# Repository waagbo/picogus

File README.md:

# PicoGUS THT

PicoGUS is a Raspberry Pi Pico based ISA sound card for DOS and Win9x retro computers.
It is a highly versatile clone card that provides near perfect emulation of the Gravis Ultrasound, Sound Blaster-series, AdLib, Tandy 3-voice and CMS/Game Blaster.

Additional features like CD-ROM (Panasonic MKE), MPU-401 and USB game controllers build further on the cards versatility and the wavetable header will further extend the capacity with a card like [X2GS from Serdaco](https://serdashop.com/products/x2gs-te) to get the original Roland magic or even a [WavetablePi](https://github.com/scrapcomputing/WavetablePiHoriz) for the ultimate all-in-one experience for MS-DOS games. 

**PicoGUS THT is a through-hole conversion of the [PicoGUS project](https://github.com/polpo/picogus).**<br />
The conversion introduces through-hole components where possible in addition to embedding new features and ideas while still keeping the card compatible with the upstream project. The design goal is to make the project be easier to solder by hand as well as giving it a higher level of retro asthetics.

PicoGUS THT exists in multiple variants based on different PicoGUS revisions. Each variant is found in their separate folder (or branch if still experimental). The different *hw* designs feature additional documentation including ready to order BOM CSVs in their respective *docs* folders.

The designs still have some TSSOP SMD chips as they do not have THT equivalents, namely the two *SN74CB3T3257PWR* level shifters (U3/U4) as well as the PCM510xA DAC. PicoGUS THT features a redesigned footprint to ease debugging in case something goes wrong.

**Note!** The hardware revisions are intentionally kept aligned with the *major* revision as the original PicoGUS boards. This is done to indicate hardware feature compatibility and to prevent confusion in case of any future major revisions of the original PicoGUS design.

### Version 1.3
This version is an extension of the PicoGUS 1.2 design while implementing the *wavetable header* with manual volume control from the *hw-hand386* branch. Together with the addition of a full size USB-A connector accessible from the computers backside this card is now a real competitor to the v2.0 SMD design.

In addition, the THT boards have also been slightly resized to optimize for component placement and JCLPCB-pricing. Progress wise, the initial design idea has been built and tested. The release version v1.3.2 is still pending build/test.

Assembly should be *EASY to MEDIUM* with the appropriate quality tools and consumables and a good project for beginners that want a little more challenge. Here is a list of recommended supplies with some personal recommendations:
* [Low Temperature Solder Paste](https://www.digikey.com/en/products/detail/chip-quik-inc/NC191LTA10/13531404) for easy soldering of SMD components.
* [Flux](https://www.digikey.com/en/products/detail/chip-quik-inc/NC191-2CC6/11480375) as it makes solder behave like magic when you need it the most.
* [Solder Wick](https://www.digikey.com/en/products/detail/chemtronics/SW14035/5177685) as it will help you when flux can't. Remember to **NEVER** pull a stuck wick.
* [Soldering Iron with J-Tip (Alientek T90B)](https://www.aliexpress.com/item/1005010015046346.html) will make the SMD components a breeze to solder. 
* [Tweezers](https://www.aliexpress.com/item/1005007298021096.html) for handling the SMD components.
* Digital Microscope of decent quality from AliExpress is very useful for visual inspection of SMD chips.
* Multimeter with good continuity tester.

### Version 2.1
This is an experimental extension of the PicoGUS 2.0 SMD design, made possible using a Waveshare Core2350B board to free enough I/O ports for the 2.0 feature set. This is still in the design phase.
<br/>

### Experimental Software Features
We have added experimental features that adds upon community ideas on top of the original software. The features are submitted as Pull Requests to the original PicoGUS repository as well but there is no guarantee that they will ever be included in the official software releases:
* DFS drive support inspired by PicoMEM so the USB drive can be accessed from MS-DOS.

<br/>

**A big thank you to [Ian Scott (polpo)](https://github.com/polpo/) for the PicoGUS design and his contributions to the retro community.**<br/>**May his work set an example for future open-source hardware projects.**

--<br/>
Vidar Waagbø, Retro City AS

## PicoGUS

The original PicoGUS project is found at [polpo/pigocus](https://github.com/polpo/picogus) or www.picogus.com.<br/>
Here are the original README.md to give some more information about the great features of the PicoGUS:

ISA sound card and CD-ROM drive emulation on the Raspberry Pi Pico's RP2040 microcontroller. PicoGUS can emulate:

* [Gravis Ultrasound (GUS)](https://en.wikipedia.org/wiki/Gravis_Ultrasound) - the primary focus of PicoGUS, hence the name
* [Sound Blaster 16](https://en.wikipedia.org/wiki/Sound_Blaster_16) (OPL3) / [Sound Blaster Pro 2](https://en.wikipedia.org/wiki/Sound_Blaster#Sound_Blaster_Pro_2,_CT1600) (OPL3) / [AdLib](https://en.wikipedia.org/wiki/Ad_Lib,_Inc.) (OPL2)
* [MPU-401 (with intelligent mode)](https://en.wikipedia.org/wiki/MPU-401) - outputs MIDI data on 3.5mm MIDI TRS connector
* [Tandy 3-voice](http://www.vgmpf.com/Wiki/index.php?title=Tandy_3_Voice)
* [CMS/Game Blaster](http://nerdlypleasures.blogspot.com/2012/10/all-you-ever-wanted-to-know-about.html)
* [Game port joystick](https://en.wikipedia.org/wiki/Game_port)
* [Panasonic/MKE CD-ROM](https://en.wikipedia.org/wiki/Panasonic_CD_interface)

Current status: perpetual beta! See the [main wiki page](https://github.com/polpo/picogus/wiki) for current status and the [compatibility list](https://github.com/polpo/picogus/wiki/Compatibility-list) for support status of various DOS programs and other system compatibility notes. This project has a heavy demoscene focus due to the GUS's history so that's what I've concentrated on, but GUS support in games is very good to excellent.

Want to buy a PicoGUS? Fully assembled PicoGUS 2.0 sound cards are available from these sources, all of whom ship worldwide:

* [Joe's Computer Museum Shop](https://jcm-1.com/product/picogus-v2/) - in US 🇺🇸
* [Serdashop](https://www.serdashop.com/PicoGUS) - in EU 🇪🇺
* [Flamelily IT](https://shop.flamelily.co.uk/picogus) - in UK 🇬🇧

Want to make your own PicoGUS? See the [build guide](https://github.com/polpo/picogus/wiki/Building-your-PicoGUS). Note that the more DIY friendly v1.1.1 hardware has some documented issues with reset – a forthcoming v1.2 revision will fix these issues. **Important caveat**: due to the specs of the Pico, assumptions made by programs written to use the GUS, the imprecise nature of emulation, and the varying specs of retro DOS PC hardware, some things will likely never be perfect. **This is still a work in progress.**

Have a PicoGUS and want to use it? See the [configuring and using your PicoGUS guide](https://github.com/polpo/picogus/wiki/Configuring-and-using-your-PicoGUS).

Want to support PicoGUS? I have a limited number of machines to test PicoGUS in and donating either money or motherboards would be greatly appreciated and help increase the compatibility of PicoGUS.

You can donate via [PayPal](https://paypal.me/ianpolpo) or Ko-Fi: 

See/hear PicoGUS in action on YouTube:

Videos by others:

My videos:

## Open Source Credits

* [Raspberry Pi Pico C/C++ SDK](https://github.com/raspberrypi/pico-sdk)
* `pico_audio_i2s` from [pico-extras](https://github.com/raspberrypi/pico-extras)
* `stdio_async_uart` from [PicoCart64](https://github.com/kbeckmann/PicoCart64)
* `gus-x.cpp` adapted from [DOSBox-X](https://github.com/joncampbell123/dosbox-x)
* OPL/AdLib emulation from [rp2040-doom](https://github.com/kilograham/rp2040-doom) (based on [emu8950](https://github.com/digital-sound-antiques/emu8950))
* MPU-401 emulation adapted from [HardMPU](https://github.com/ab0tj/HardMPU) and [DOSBox-X](https://github.com/joncampbell123/dosbox-x)
* Tandy 3-voice emulation based on code contributed by [Aaron Giles](https://aarongiles.com/), adapted from [DREAMM](https://aarongiles.com/dreamm/) 
* CMS emulation based on code contributed by [Aaron Giles](https://aarongiles.com/), adapted from [DREAMM](https://aarongiles.com/dreamm/)
* USB support uses [TinyUSB](https://github.com/hathach/tinyusb) and [tusb_xinput](https://github.com/Ryzee119/tusb_xinput) with USB mass storage improvements by rppicomidi and wbcbz7.
* FAT drive support by [FatFS](https://elm-chan.org/fsw/ff/)

## License

The hardware portions of this repository (hw/ directory) are licensed under the CERN OHL version 2, permissive.

The software portions of this repository (sw/, pgusinit/ directories) as a collection are licensed under the GNU GPL version 2. Some files are individually dual-licensed under BSD or MIT licenses – see the license in the file headers for details.

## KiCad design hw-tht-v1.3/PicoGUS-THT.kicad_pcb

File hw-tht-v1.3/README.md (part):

# PicoGUS THT (through-hole) v1.3.2 – based on PicoGUS v1.2

Board revision **v1.3.2**: the v1.3.1 (rev B) THT board on a 102 mm outline, with
the fine-pitch chips soldered straight to the card and a test pad on every one of their pins.

* **U3/U4** (SN74CB3T3257, TSSOP-16) and **U9** (PCM5102A, TSSOP-20; the PCM5100A/5101A fit too) only exist as TSSOPs. They are soldered to
  the card on hand-solder footprints, and **every pin has its own 0.7 mm round test pad** in line with it, for a
  probe, a meter or a scope (see [U3/U4 and U9 with a test pad per pin](#u3u4-and-u9-with-a-test-pad-per-pin)).
  The TSSOP-to-DIP adapter boards of the earlier v1.3.2 layout are gone, and so are their sockets.
* **The GY-PCM5102 module option (J10) is gone.** The on-board DAC is always fitted.
* **New placement** of the DAC block, the mixer and the jacks (2026-10-31 / 2026-11-01): the DAC sits above U3/U4
  with its analog side facing east toward the output filter and the mixer above it, MIDI OUT at the top of the
  bracket end and LINE OUT below WT VOL (see [Placement](#placement)).
* **C36** (U9 charge-pump decoupling) is a through-hole 0.1 µF disc, and all eight DAC decoupling discs sit on the
  side of U9 where their pins are (see [DAC decoupling](#dac-decoupling)).
* **C8/C10** (U8 PSRAM decoupling) are the v1.3.1 through-hole discs, next to U8.
* **1.84 mm shorter**: 102.0 mm long over the outline (v1.3.1: 103.8 mm), trimmed at the bracket end. The bracket tab
  holes H1/H2 are 1.70 mm further from the bracket plate, so the card needs a bracket with longer tabs (see
  [Bracket](#bracket)).
* **No artwork on the back silkscreen**: the princess artwork is to be UV printed instead. The back texts stay.

The main board is through-hole apart from **U3, U4, U9** (TSSOP, 0.65 mm pitch), **U8** (APS6404L PSRAM, SOIC-8,
1.27 mm pitch) and the optional **U12** (USBLC6-2SC6, SOT-23-6), all on the front. The rest of the circuit is
v1.3.1's: USB-A host port, Waveblaster header, op-amp mixer.

> **Status: v1.3.2, ready to order (tag `hw-tht-v1.3.2`); not built or tested yet.** The placement of 2026-11-01 is
> routed on two layers (2026-11-01).
> The schematic's ERC is the same as v1.3.1's (280 warnings, 0 errors). DRC with schematic parity finds 0
> unconnected items and, as errors, only the 12 accepted courtyard overlaps in the logic column, so
> `hw-common/tools/jlcpcb.sh` exports with `ALLOW_DRC=courtyards_overlap`; `build/jlcpcb/` holds that export (not in git: the repository
> ignores `build/`). The first routed TSSOP layout (commit 298e993) was reviewed independently; this placement
> shortens the DAC outputs and the mixer's summing nodes that review pointed at, and its route applies the review's
> rules from the start. Compared with the routed DIP-adapter layout (commit d5c4a85) it is better on I2S, the
> DAC-to-mixer path and the vias at silkscreen text, and worse on the ISA data-bus length, which the test pads set:
> see [Layout status](#layout-status).

Files:

| File | What |
|---|---|
| `PicoGUS-THT.kicad_pro/.kicad_sch/.kicad_pcb` | KiCad **10** project (the root sheet is the v1.2 logic). The board is routed |
| `audio.kicad_sch` | PCM510x DAC sheet: U9 a TSSOP-20 with test pads, C36 a THT disc, no J10 |
| `wavetable.kicad_sch` | Waveblaster header, WT volume, op-amp mixer, line-out jack (as v1.3.1) |
| `usb.kicad_sch` | USB host port (J11 USB-A, F1, C34/C35, U12) (as v1.3.1) |
| `PicoGUS-THT-schematic.pdf` | Schematic PDF |
| `docs/BOM-THT.csv` | BOM with DigiKey **and** LCSC part numbers, stock (2026-11-07) and a digikey.no link per line |
| `docs/BOM-THT-digikey.csv`, `docs/BOM-THT-lcsc.csv` (+ `-optional`) | DigiKey and LCSC upload files for one board, made from `BOM-THT.csv` (see [Ordering](#ordering)); optional: sockets, U12 |
| `docs/BOM-THT-sockets.csv` (+ `-digikey-optional`, `-lcsc-optional`) | Socket build: every DIP IC and the Pico socketed, with heights (see [Socket build](#socket-build)) |
| `docs/renders/` | 3D renders of the routed card: red from the front and the back, green, purple, white and black from the front (ENIG; white silkscreen, black on white). Made with `hw-common/tools/render.sh` |
| `docs/figures/` | Figures for the README's exceptions and design choices (e.g. the test pads, the placement options, the accepted courtyard overlaps), with the scripts that make them in `docs/figures/src/` |

The shared `PiGUS library` symbols and footprints are linked from `hw-common/`, like the other boards. **New in the
shared library for v1.3.2:** `TSSOP-16_4.4x5mm_P0.65mm_HandSolder_TestPads` (U3, U4),
`TSSOP-20_4.4x6.5mm_P0.65mm_HandSolder_TestPads` (U9) and `RPi_Pico_SMD_TH_USB_NoSWD` (U1, see
[102 mm board](#102-mm-board)), in `hw-common/PiGUS library.pretty`; DRC's library check finds the board's U1, U3,
U4 and U9 identical to them. The adapter footprints and adapter 3D models of the earlier v1.3.2 layout are removed;
the older `DIP-16_W7.62mm_TSSOP-16_Nested` stays unused.

Every part has a 3D model. The ones KiCad 10's library does not have are in `hw-common/parts`, reached through the
project folder's `parts` link: the CUI SJ1-3535NG jacks (J8 green; J5 a black copy of the same CUI model), the Alps
RK09712 pot (RV1) and a simple generated Bourns MF-R050 (F1). U3/U4/U9 use KiCad's TSSOP models, U1 KiCad's own
`RaspberryPi_Pico.step`, and J9's header model path is fixed. The library footprints carry the same models as the
board.

## What changed compared to v1.3.1

### U3/U4 and U9 with a test pad per pin

| | U3, U4 (SN74CB3T3257, TSSOP-16) | U9 (PCM5102A, TSSOP-20) |
|---|---|---|
| Footprint | `PiGUS library:TSSOP-16_4.4x5mm_P0.65mm_HandSolder_TestPads` | `PiGUS library:TSSOP-20_4.4x6.5mm_P0.65mm_HandSolder_TestPads` |
| Courtyard | 11.4 × 5.75 mm | 11.4 × 7.05 mm |
| Position (centre) | U3 (150.22, 110.10), U4 (161.44, 110.12), both 90° (pin 1 at the bottom left) | (156.10, 84.53), 180° (pin 1 at the bottom right) |

* **Land pattern**: the TSSOP hand-solder pads (1.775 × 0.40 mm at ±3.01 mm from the centre, toes out to ±3.9 mm),
  long enough to put an iron on each pin.
* **One test pad per pin**: a 0.7 mm round pad (bare copper, `testpoint` property) straight out from each pin,
  joined to it by a 0.2 mm track. The pads alternate between two columns, 4.45 and 5.10 mm from the centre, so each
  sits on its own pin's line and 1.3 mm from the next pad in its column; the track to an outer pad passes between two
  inner pads with 0.2 mm on each side, the board's normal clearance. The footprint has the pin numbers at the column
  ends in 0.8 mm silk. The pads make every pin reachable for a probe, a meter or a scope clip, and a solder bridge
  between two pins shows up as a short between their pads.
* **Routing**: an outer-column pin is routed from its test pad. An inner-column pin that is used gets a 0.2 mm
  escape stub straight on from its test pad, centred between the two outer pads, to 5.80 mm from the centre, and is
  routed from the stub end (26 stubs; the two left unused are removed after routing, see
  [Layout status](#layout-status)). The router cannot squeeze a track between two outer pads (0.6 mm
  gap) any other way, and the stubs keep the 0.2 mm clearance exactly as the pin-to-pad tracks do.
* **Pin numbers stay the schematic's**: U9 is 1 CPVDD, 2 CAPP, 3 CPGND, 4 CAPM, 5 VNEG, 6 OUTL, 7 OUTR, 8 AVDD,
  9 AGND, 10 DEMP, 11 FLT, 12 SCK, 13 BCK, 14 DIN, 15 LRCK, 16 FMT, 17 XSMT, 18 LDOO, 19 DGND, 20 DVDD.
* The symbols' `Adapter` fields and the adapter wording in the descriptions and sheet notes are gone; the root sheet
  says "SMD: U3/U4 TSSOP-16, U9 TSSOP-20 (with test pads), U8 SOIC-8, U12 opt.".

![Test pads on U9 (and U3/U4): the TSSOP-20 land pattern to scale with its 20 test pads in two staggered columns
(inner 4.45 mm, outer 5.10 mm from the centre, 1.3 mm between two pads of a column), the 0.2 mm track from each pin
to its pad passing between two pads with 0.2 mm clearance on each side, and the escape stubs that carry an
inner-column pin out between two outer pads to the routing](docs/figures/test-pads.png)

### No GY-PCM5102 module option

J10 (the GY-PCM5102 module, soldered on male pins over the DAC area as the alternative to the on-board DAC since
v1.3.0) is gone from the schematic and the board. Its dashed silkscreen outline and the "DAC -OR- GY-PCM5102"
heading went with it; the heading now just says "DAC". Its nets (BCK, DIN, LRCK, +5V, GND, AUDIO_L/R) stay,
because U9's circuit uses them. U9, C12–C20, C36, FB3, R7 and R8 are always fitted. The BOM's J10 line and its
"DAC AREA: leave out ..." notes are gone.

### DAC decoupling

C36 (U9 CPVDD decoupling) is the board's standard 0.1 µF 50 V X7R radial disc (Murata RDER71H104K0M1H03A, the 0.1 µF
line of the BOM) instead of v1.3.1's 0603. U9 stands at 180° with its analog pins 1–10 facing east, toward the output
filter and the mixer, and its digital pins 11–20 facing west. Each disc sits on the side of the pins it serves:

* **East, beside pins 1–10**, in rows 3.0 mm apart: C15 (AVDD, 10 µF) and C13 (AVDD) at the top, the output
  resistors R8/R7 level with pins 7/6, then C16 (CAPP/CAPM) and C17 (VNEG); the filter discs C20/C19 end the C13 and
  C16 rows on the east.
* **South, under pins 1–3**: C36 (CPVDD/CPGND), with C14 (+3V3) below it.
* **West, beside pins 11–20**: C18 (LDOO) level with pins 17–19 and C12 (DVDD) below pin 20. FB3 (the AVDD bead)
  runs along the top of the block from the +3V3 side in the west to its AVDD pad above C15.

Distances from the chip pin to the nearest pad of the part, straight line:

| Part | Pins | DIP-adapter layout (d5c4a85) | First routed TSSOP layout (298e993) | Now |
|---|---|---|---|---|
| C36 | CPVDD (1) / CPGND (3) | 2.7 / 9.2 mm | 9.7 / 5.6 mm | 3.6 / 5.4 mm |
| C16 | CAPP (2) / CAPM (4) | 3.2 / 3.2 mm | 9.5 / 4.6 mm | 9.7 / 5.5 mm |
| C17 | VNEG (5) | 6.6 mm | 9.6 mm | 8.1 mm |
| C13 | AVDD (8) / AGND (9) | 4.7 / 6.7 mm | 5.1 / 9.6 mm | 5.6 / 9.9 mm |
| C15 | AVDD (8) | 7.3 mm | 12.4 mm | 7.8 mm |
| C18 | LDOO (18) / DGND (19) | 3.5 / 9.1 mm | 4.5 / 9.5 mm | 4.0 / 9.0 mm |
| C12 | DVDD (20) / DGND (19) | 4.5 / 8.4 mm | 2.6 / 6.4 mm | 5.4 / 3.8 mm |
| R7 / R8 | OUTL (6) / OUTR (7) | 3.0 / 2.8 mm | 6.8 / 8.2 mm | 4.7 / 4.6 mm |
| FB3 | AVDD (8) | 2.8 mm | 14.1 mm | 6.3 mm |

* **C36 is the nearest disc to its pin** (3.6 mm from CPVDD), as the PCM510x datasheet asks for the charge-pump
  supply. C16 (the flying capacitor between CAPP and CAPM) stays 9.7 mm from CAPP: it shares the east column with
  the output resistors, which sit level with their pins.
* C16 and C17 were 0.02 mm off the 3.0 mm row grid in the uploaded placement (y 88.60 / 91.60), so C16's courtyard
  touched R7's by 0.015 mm; they are now at y 88.62 / 91.62, in line with C19.
### C8/C10: through-hole discs next to U8

| Ref | Part | DigiKey | LCSC |
|---|---|---|---|
| C8 | 0.1 µF 50 V X7R radial disc, 5.0 mm pitch, Murata RDER71H104K0M1H03A (the BOM's 0.1 µF line) | 490-9144-1-ND | C527620 |
| C10 | 1 µF 50 V X7R radial disc, 5.0 mm pitch, Murata RDER71H105K2M1H03A | 490-9146-1-ND | C1620132 |

These are the v1.3.1 parts again (the routed layout of commit 8dbb6c6 had 0805s on the back under U8). U8 (SOIC-8,
front) stands at 90° at (190.00, 92.47): pins 1–4 along the bottom (y 94.95, pin 1 at the left), pins 5–8 along the
top (y 90.00), pin 8 (+3V3) at (188.09, 90.00), pins 3/4/7 GND. C8 (0.1 µF) stands vertically left of U8, its +3V3
pad 2.50 mm straight left of pin 8 at (185.59, 90.00) and its GND pad at (185.59, 95.00); C10 (1 µF) lies above U8,
+3V3 pad at (187.09, 87.00), GND pad at (192.09, 87.00). With them, every SMD part (U3, U4, U8, U9, U12) is on the
front.

### 102 mm board

The bracket end of the outline is trimmed 1.84 mm (x 220.13 → 218.29). The board is 101.90 × 99.85 mm at the
outline's line centres, 102.00 × 99.95 mm over its 0.1 mm lines (v1.3.1 and the routed v1.3.2 layout: 103.74 ×
99.85 / 103.84 × 99.95 mm). JLCPCB quoted USD 24.50 for 10 black ENIG 2-layer boards at 102.0 mm (and 101.9 mm), USD 33 at
102.7 mm and 33.53 at 103.74 mm (2026-10-28). The ISA fingers, the other three edges and the bracket plate's place in the case do not change.
To keep copper at least 0.35 mm from the new edge, these parts moved left, away from the bracket:

| Part | Moved | Now | Nearest copper to the new edge |
|---|---|---|---|
| H1 / H2 (bracket tab holes) | 1.70 mm | x 214.70 | 0.39 mm (their 6.4 mm pads) |
| J5 (MIDI out) | 1.10 mm | x 217.00 | 0.39 mm (sleeve pad) |
| J8 (line out) | 0.90 mm | x 217.00 | 0.39 mm (sleeve pad) |
| U1 (Pico), with its five test-pad rule areas and its two micro-USB relief slots | 1.35 mm | centre x 192.88, pin 1 (217.01, 100.00) | 0.36 mm (TP2/TP3); the slots (centre x 216.88) end 0.41 mm from the edge |
| U4 / U3 | – | TSSOP centres x 161.44 / 150.22 (re-placed for the soldered TSSOPs, see [Placement](#placement)) | – |

J11 and RV1 stay where they were. The distances are to the outline's line centre. Between these parts and the edge
there is no room for a track or a via: 0.3 mm copper-to-edge, a 0.2 mm track and 0.2 mm clearance need 0.7 mm. What
the trim means for the bracket is under [Bracket](#bracket): the tab holes need a bracket with 1.70 mm longer tabs.

![The bracket end trimmed from 103.74 to 101.90 mm: old (dashed) and new outline with the trimmed 1.84 mm strip, the
bracket plate and tabs from User.Drawings, the tab holes H1/H2 1.70 mm further in (7.03 mm from the plate instead of
5.33), J5, RV1, J8, J11 and the Pico's USB end with their moves and nearest copper to the new edge, and a table of the
x positions](docs/figures/bracket-trim.png)

* **U1 uses the new footprint `PiGUS library:RPi_Pico_SMD_TH_USB_NoSWD`**: `RPi_Pico_SMD_TH_USB` without the
  three SMD castellation pads at the SWD end (pads 41–43: SWCLK and SWDIO, both not connected, and GND; their
  through-holes stay) and with the courtyard 0.2 mm past the module there instead of 0.5 mm. With the old
  courtyard, U4's would overlap the Pico's by 0.25 mm.
* The Pico's USB end (x 218.38) is now flush with the edge: 0.09 mm past the outline's line centre (0.40 mm inside
  it before).
* The Pico's far end is at x 167.38, 2.9 mm under a full-size Waveblaster daughterboard's outline (x 170.32; routed
  v1.3.2 layout 1.6 mm, v1.3.1 1.3 mm). That matters for a socketed Pico (see [Socket build](#socket-build)).

### Placement

The board holds a hand arrangement on the 102 mm outline: the logic column and the Pico from 2026-10-28, the jack
arrangement for the soldered TSSOPs from 2026-10-31, and the DAC block and mixer as rearranged on 2026-11-01 after a
first route, routed afterwards (see [Layout status](#layout-status)).

* **Logic column at the left edge** (as on the earlier v1.3.2 layout). U10, U7, U6 and U5 (DIP-14, 90°, pin 1 at the
  left as on v1.3.1) are stacked in line with U2 at x 120.07, 12.05 mm apart (pin 1 at y 65.62 / 77.67 / 89.71 /
  101.76; U2: 113.81). Each chip's decoupling cap lies horizontally (0°) in the gap above it, pad 1 2.21 mm straight
  above the supply pin (pin 14; U2: pin 20): C21 (U10, +5V), C6 (U7), C9 (U6), C7 (U5) and C4 (U2), pads at x
  120.07 / 125.07, y 55.79 / 67.83 / 79.88 / 91.93 / 103.97. R18, R5, R6 and R17 stand vertically (−90°) in one
  column at x 138.60, at the chips' right-hand ends (pad 1 at y 56.73 / 68.78 / 80.82 / 92.87). The column is
  packed tighter than the courtyards allow: 12 overlaps, accepted (see [Layout status](#layout-status)). The five
  references stand vertically at the board edge (x 117.50), centred on each chip.
* **U2** (DIP-20, 90°) at the lower left, pin 1 (120.07, 113.81). **J1** (the IRQ/DMA jumper block) at pin 1
  (136.03, 124.91), 90°, with its `IRQ`/`DMA` labels and numbers above it.
* **U3/U4** (TSSOP-16 with test pads, 90°): U3 (D0–D3, A0–A3) at (150.22, 110.10) and U4 (D4–D7, A4–A7) at
  (161.44, 110.12), pin 1 at the bottom left. Their decoupling discs C3/C5 lie above them at y 102.29 (C3's +3V3 pad
  at x 147.88, 4.8 mm from U3's pin 16), R2 at (160.97, 99.01).
* **DAC block, above U3/U4 and the Pico's far end**: U9 (TSSOP-20 with test pads) at (156.10, 84.53), 180°: pins
  11–20 (I2S, LDOO, DGND, DVDD) on its west side, pins 1–10 (charge pump, VNEG, outputs, AVDD, AGND) on its east side,
  facing the output filter and the mixer. East of it, in rows 3.0 mm apart (see [DAC decoupling](#dac-decoupling)):
  C15 (163.60, 76.53), C13 (168.60, 79.53), R8 (163.60, 82.60), R7 (163.62, 85.62), C16 (168.60, 88.62) and C17
  (163.60, 91.62), with the filter discs C20 (170.70, 79.53) and C19 (170.70, 88.62) at the east end. C36 (161.00,
  90.50) and C14 (156.00, 93.50) lie under U9's pins 1–3, C18 (149.10, 86.03) and C12 (153.60, 90.53) on its west
  side, and FB3 (the AVDD bead) along the top at (148.60, 77.03). `DAC` stands at (146.11, 92.10).
* **Mixer, above the DAC block**: U11 (DIP-8, 0°) at (173.00, 61.00), its feedback discs C30/C31 standing (90°) at
  its two ends, (170.12, 65.08) and (183.50, 67.00); C28 (+12VA) above it at (180.62, 54.08) and C29 (−12VA) below at
  (175.62, 75.08); R23/R24 (±12V 10 Ω) at (170.42, 57.50) / (170.42, 72.00); C32/C33 (47 µF) standing at x 184.62
  (y 57.12 / 70.08). The mixer resistors stay in two columns: R13, R11, R22, R10, R21 at x 189.43 (y 54.50 / 58.00 /
  65.00 / 72.50 / 79.50) and R20, R12, R19 at x 199.58 (y 61.50 / 69.00 / 76.00). `MIXER` at (171.12, 55.04).
* **C22/C23** (the 10 µF bipolar Waveblaster coupling caps) stand at the top next to J9, (174.00, 40.00) and
  (181.50, 40.00), −90°, with their references above them at y 38.00. C22's can is 0.48 mm outside a full-size
  daughterboard's outline (x 170.32) at nominal size.
* **Bracket end, top to bottom: MIDI OUT, WT VOL, LINE OUT.** J5 (MIDI out) at (217.00, 49.00) with its parts
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
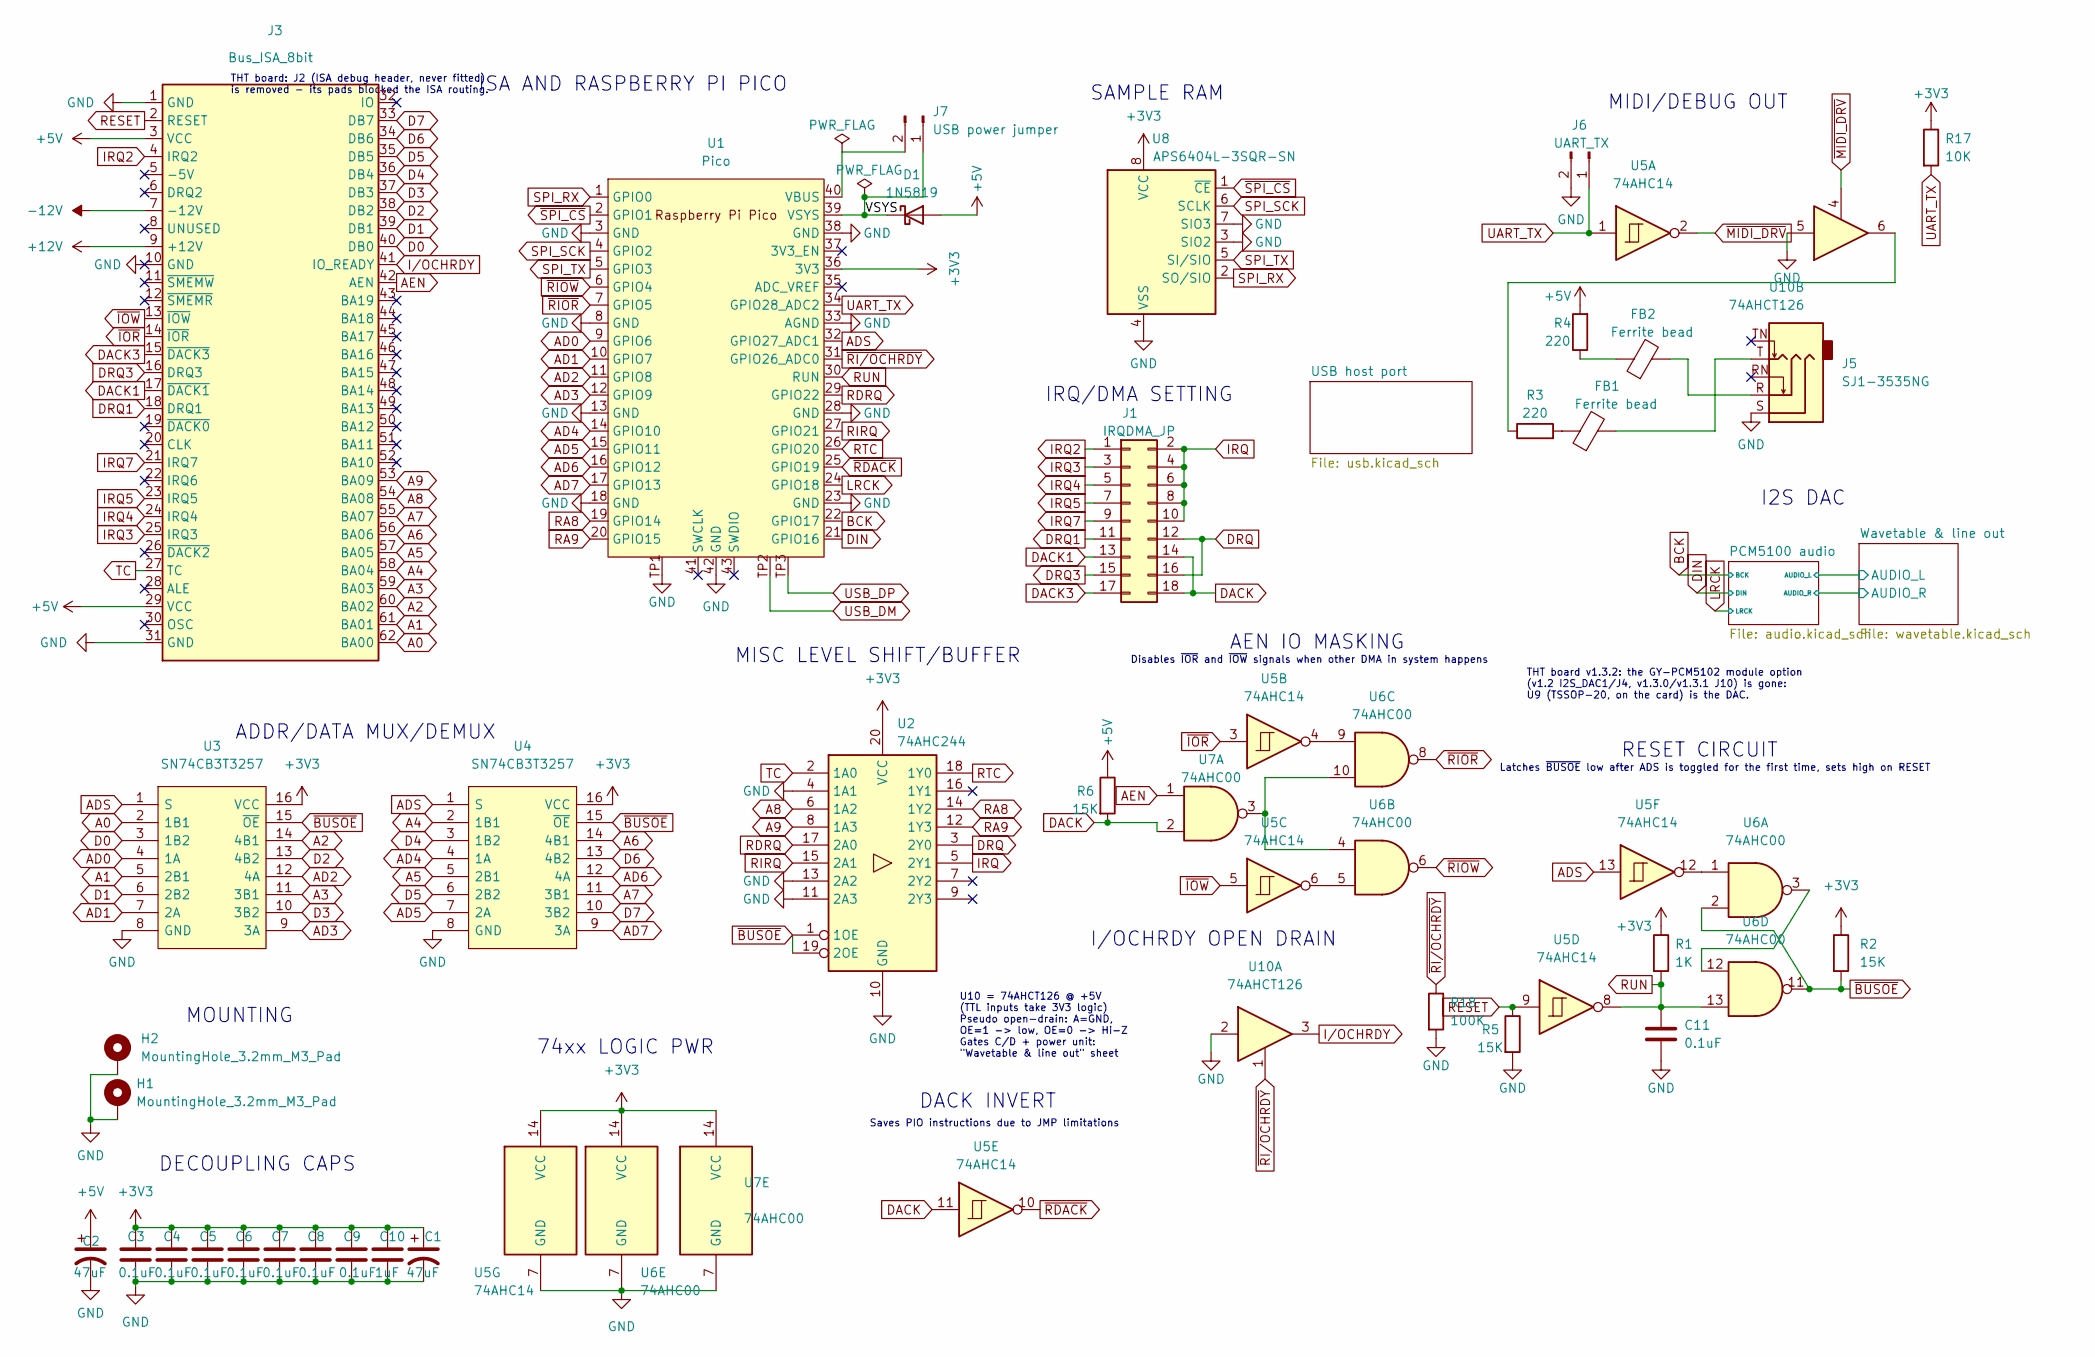
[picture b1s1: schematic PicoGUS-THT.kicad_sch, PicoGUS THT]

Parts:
C1, C2: 47uF; CP_Radial_D5.0mm_P2.00mm; MPN 35YXJ47M5X11; DigiKey 1189-2919-ND
C3, C4, C5, C6, C7, C8, C9, C11: 0.1uF; C_Disc_D5.0mm_W2.5mm_P5.00mm; MPN RDER71H104K0M1H03A; DigiKey 490-9144-1-ND
C10: 1uF; C_Disc_D5.0mm_W2.5mm_P5.00mm; MPN RDER71H105K2M1H03A; DigiKey 490-9146-1-ND
D1: 1N5819; D_DO-41_SOD81_P10.16mm_Horizontal; MPN 1N5819RLG; DigiKey 1N5819RLGOSCT-ND
FB1, FB2: Ferrite bead; R_Axial_DIN0309_L9.0mm_D3.2mm_P12.70mm_Horizontal; MPN 2743002112; DigiKey 1934-1477-1-ND
H1, H2: MountingHole_3.2mm_M3_Pad
J1: IRQDMA_JP; PinHeader_2x09_P2.54mm_Vertical; MPN 10129381-918001BLF; DigiKey 609-10129381-918001BLF-ND
J3: Bus_ISA_8bit; BUS_PC_chamfer
J5: SJ1-3535NG; Jack_3.5mm_CUI_SJ1-3535NG_Horizontal; MPN SJ1-3535NG; DigiKey CP1-3535NG-ND
J6: UART_TX; PinHeader_1x02_P2.54mm_Vertical; MPN PREC040SAAN-RC; DigiKey S1012EC-40-ND
J7: USB power jumper; PinHeader_1x02_P2.54mm_Vertical; MPN PREC040SAAN-RC; DigiKey S1012EC-40-ND
R1: 1K; R_Axial_DIN0207_L6.3mm_D2.5mm_P10.16mm_Horizontal; MPN MFR-25FBF52-1K; DigiKey 1.00KXBK-ND
R2, R5, R6: 15K; R_Axial_DIN0207_L6.3mm_D2.5mm_P10.16mm_Horizontal; MPN MFR-25FBF52-15K; DigiKey 15.0KXBK-ND
R3, R4: 220; R_Axial_DIN0207_L6.3mm_D2.5mm_P10.16mm_Horizontal; MPN RNMF14FTC220R; DigiKey S220CACT-ND
R17: 10K; R_Axial_DIN0207_L6.3mm_D2.5mm_P10.16mm_Horizontal; MPN MFR-25FBF52-10K; DigiKey 10.0KXBK-ND
R18: 100K; R_Axial_DIN0207_L6.3mm_D2.5mm_P10.16mm_Horizontal; MPN MFR-25FBF52-100K; DigiKey 100KXBK-ND
U1: Pico; RPi_Pico_SMD_TH_USB_NoSWD; MPN SC0915; DigiKey 2648-SC0915CT-ND
U2: 74AHC244; DIP-20_W7.62mm; MPN SN74AHC244N; DigiKey 296-4585-5-ND
U3, U4: SN74CB3T3257; TSSOP-16_4.4x5mm_P0.65mm_HandSolder_TestPads; MPN SN74CB3T3257PWR; DigiKey 296-17850-1-ND
U5: 74AHC14; DIP-14_W7.62mm; MPN SN74AHC14N; DigiKey 296-4550-5-ND
U6, U7: 74AHC00; DIP-14_W7.62mm; MPN SN74AHC00N; DigiKey 296-4510-5-ND
U8: APS6404L-3SQR-SN; SOIC-8_3.9x4.9mm_P1.27mm; MPN APS6404L-3SQR-SN; DigiKey 1528-4677-ND (Adafruit 4677 (64Mbit QSP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
U10: 74AHCT126; DIP-14_W7.62mm; MPN SN74AHCT126N; DigiKey 296-4659-5-ND

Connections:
+3V3: C1.1, C3.1, C4.1, C5.1, C6.1, C7.1, C8.1, C9.1, C10.1, R1.1, R2.1, R17.1, U1.36 (3V3), U2.20 (VCC), U3.16 (VCC), U4.16 (VCC), U5.14 (VCC), U6.14 (VCC), U7.14 (VCC), U8.8 (VCC); also elsewhere on the board
+5V: C2.1, D1.2 (A), J3.3 (VCC), J3.29 (VCC), R4.2, R6.1; also elsewhere on the board
+12V: J3.9 (+12V); also elsewhere on the board
-12V: J3.7 (-12V); also elsewhere on the board
/VSYS: D1.1 (K), J7.1, U1.39 (VSYS)
A0: J3.62 (BA00), U3.2 (1B1)
A1: J3.61 (BA01), U3.5 (2B1)
A2: J3.60 (BA02), U3.14 (4B1)
A3: J3.59 (BA03), U3.11 (3B1)
A4: J3.58 (BA04), U4.2 (1B1)
A5: J3.57 (BA05), U4.5 (2B1)
A6: J3.56 (BA06), U4.14 (4B1)
A7: J3.55 (BA07), U4.11 (3B1)
A8: J3.54 (BA08), U2.6 (1A2)
A9: J3.53 (BA09), U2.8 (1A3)
AD0: U1.9 (GPIO6), U3.4 (1A)
AD1: U1.10 (GPIO7), U3.7 (2A)
AD2: U1.11 (GPIO8), U3.12 (4A)
AD3: U1.12 (GPIO9), U3.9 (3A)
AD4: U1.14 (GPIO10), U4.4 (1A)
AD5: U1.15 (GPIO11), U4.7 (2A)
AD6: U1.16 (GPIO12), U4.12 (4A)
AD7: U1.17 (GPIO13), U4.9 (3A)
ADS: U1.32 (GPIO27_ADC1), U3.1 (S), U4.1 (S), U5.13
AEN: J3.42 (AEN), U7.1
BCK: U1.22 (GPIO17); also elsewhere on the board
D0: J3.40 (DB0), U3.3 (1B2)
D1: J3.39 (DB1), U3.6 (2B2)
D2: J3.38 (DB2), U3.13 (4B2)
D3: J3.37 (DB3), U3.10 (3B2)
D4: J3.36 (DB4), U4.3 (1B2)
D5: J3.35 (DB5), U4.6 (2B2)
D6: J3.34 (DB6), U4.13 (4B2)
D7: J3.33 (DB7), U4.10 (3B2)
DACK: J1.14, J1.18, R6.2, U5.11, U7.2
DACK1: J1.13, J3.17 (~DACK1)
DACK3: J1.17, J3.15 (~DACK3)
DIN: U1.21 (GPIO16); also elsewhere on the board
DRQ: J1.12, J1.16, U2.3 (2Y0)
DRQ1: J1.11, J3.18 (DRQ1)
DRQ3: J1.15, J3.16 (DRQ3)
GND: C1.2, C2.2, C3.2, C4.2, C5.2, C6.2, C7.2, C8.2, C9.2, C10.2, C11.2, H1.1, H2.1, J3.1 (GND), J3.10 (GND), J3.31 (GND), J5.S, J6.2, R5.2, R18.2, U1.3 (GND), U1.8 (GND), U1.13 (GND), U1.18 (GND), U1.23 (GND), U1.28 (GND), U1.33 (AGND), U1.38 (GND), U1.42 (GND), U1.TP1, U2.4 (1A1), U2.10 (GND), U2.11 (2A3), U2.13 (2A2), U3.8 (GND), U4.8 (GND), U5.7 (GND), U6.7 (GND), U7.7 (GND), U8.3 (SIO2), U8.4 (VSS), U8.7 (SIO3), U10.2, U10.5; also elsewhere on the board
IRQ: J1.2, J1.4, J1.6, J1.8, J1.10, U2.5 (2Y1)
IRQ2: J1.1, J3.4 (IRQ2)
IRQ3: J1.3, J3.25 (IRQ3)
IRQ4: J1.5, J3.24 (IRQ4)
IRQ5: J1.7, J3.23 (IRQ5)
IRQ7: J1.9, J3.21 (IRQ7)
I/OCHRDY: J3.41 (IO_READY), U10.3
LRCK: U1.24 (GPIO18); also elsewhere on the board
unnamed: FB1.1, R3.2
unnamed: FB1.2, J5.T
unnamed: FB2.1, R4.1
unnamed: FB2.2, J5.R
unnamed: J7.2, U1.40 (VBUS)
unnamed: R3.1, U10.6
unnamed: U5.4, U6.9
unnamed: U5.6, U6.5
unnamed: U5.12, U6.1
unnamed: U6.4, U6.10, U7.3
unnamed: U6.3, U6.12
RA8: U1.19 (GPIO14), U2.14 (1Y2)
RA9: U1.20 (GPIO15), U2.12 (1Y3)
RDRQ: U1.29 (GPIO22), U2.17 (2A0)
RESET: J3.2 (RESET), R5.1, U5.9; also elsewhere on the board
RIRQ: U1.27 (GPIO21), U2.15 (2A1)
RTC: U1.26 (GPIO20), U2.18 (1Y0)
RUN: C11.1, R1.2, U1.30 (RUN), U5.8, U6.13
SPI_RX: U1.1 (GPIO0), U8.2 (SO/SIO)
SPI_SCK: U1.4 (GPIO2), U8.6 (SCLK)
SPI_TX: U1.5 (GPIO3), U8.5 (SI/SIO)
TC: J3.27 (TC), U2.2 (1A0)
UART_TX: J6.1, R17.2, U1.34 (GPIO28_ADC2), U5.1
USB_DM: U1.TP2; also elsewhere on the board
USB_DP: U1.TP3; also elsewhere on the board
~BUSOE: R2.2, U2.1 (1OE), U2.19 (2OE), U3.15 (~OE), U4.15 (~OE), U6.2, U6.11
~IOR: J3.14 (~IOR), U5.3
~IOW: J3.13 (~IOW), U5.5
~MIDI_DRV: U5.2, U10.4; also elsewhere on the board
~RDACK: U1.25 (GPIO19), U5.10
~RIOR: U1.7 (GPIO5), U6.8
~RIOW: U1.6 (GPIO4), U6.6
~RI/OCHRDY: R18.1, U1.31 (GPIO26_ADC0), U10.1
~SPI_CS: U1.2 (GPIO1), U8.1 (~CE)

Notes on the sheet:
Saves PIO instructions due to JMP limitations
DECOUPLING CAPS
I2S DAC
Disables ~{IOR} and ~{IOW} signals when other DMA in system happens
Latches ~{BUSOE} low after ADS is toggled for the first time, sets high on RESET
MIDI/DEBUG OUT
MOUNTING
MISC LEVEL SHIFT/BUFFER
IRQ/DMA SETTING
DACK INVERT
ADDR/DATA MUX/DEMUX
SAMPLE RAM
AEN IO MASKING
ISA AND RASPBERRY PI PICO
RESET CIRCUIT
I/OCHRDY OPEN DRAIN
74xx LOGIC PWR
U10 = 74AHCT126 @ +5V (TTL inputs take 3V3 logic) Pseudo open-drain: A=GND, OE=1 -> low, OE=0 -> Hi-Z Gates C/D + power unit: "Wavetable & line out" sheet
THT board v1.3.2: the GY-PCM5102 module option (v1.2 I2S_DAC1/J4, v1.3.0/v1.3.1 J10) is gone: U9 (TSSOP-20, on the card) is the DAC.
THT board: J2 (ISA debug header, never fitted) is removed - its pads blocked the ISA routing.

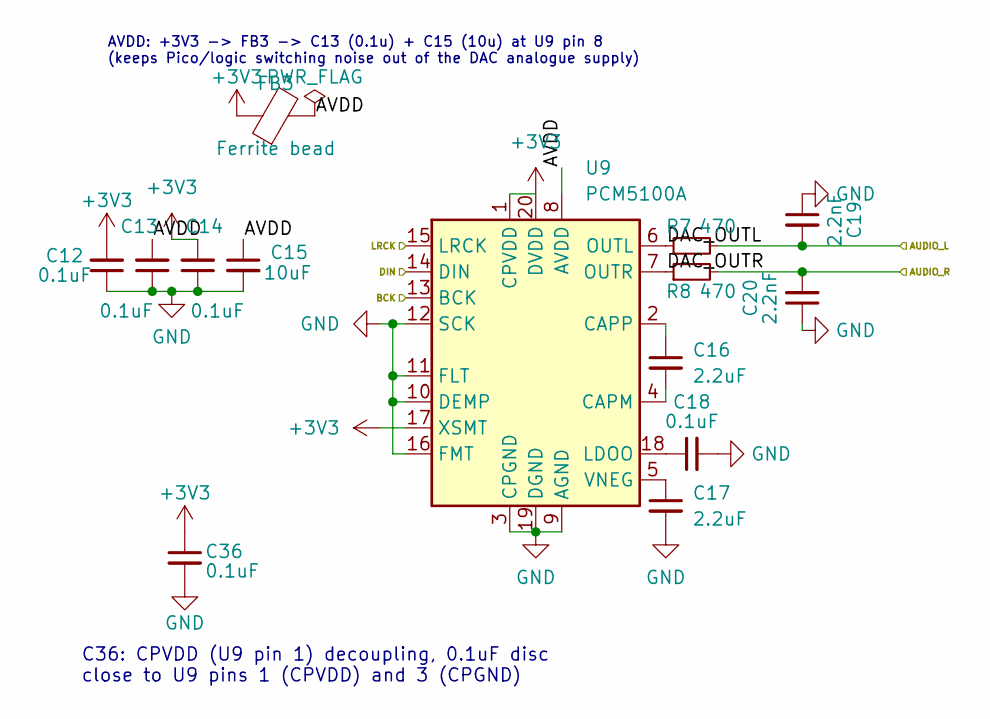
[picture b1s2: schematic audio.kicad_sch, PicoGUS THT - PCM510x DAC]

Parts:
C12, C13, C14, C18, C36: 0.1uF; C_Disc_D5.0mm_W2.5mm_P5.00mm; MPN RDER71H104K0M1H03A; DigiKey 490-9144-1-ND
C15: 10uF; C_Disc_D5.0mm_W2.5mm_P5.00mm; MPN RCER71H106MWM1H03A; DigiKey 490-7518-1-ND
C16, C17: 2.2uF; C_Disc_D5.0mm_W2.5mm_P5.00mm; MPN FG24X7R1H225KRT06; DigiKey 445-173378-1-ND
C19, C20: 2.2nF; C_Disc_D5.0mm_W2.5mm_P5.00mm; MPN FG28C0G1H222JNT06; DigiKey 445-173487-1-ND
FB3: Ferrite bead; R_Axial_DIN0309_L9.0mm_D3.2mm_P12.70mm_Horizontal; MPN 2743002112; DigiKey 1934-1477-1-ND
R7, R8: 470; R_Axial_DIN0207_L6.3mm_D2.5mm_P10.16mm_Horizontal; MPN RNMF14FTC470R; DigiKey S470CACT-ND
U9: PCM5100A; TSSOP-20_4.4x6.5mm_P0.65mm_HandSolder_TestPads; MPN PCM5100APWR; DigiKey 296-36705-1-ND

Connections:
+3V3: C12.2, C14.2, C36.1, FB3.1, U9.1 (CPVDD), U9.17 (XSMT), U9.20 (DVDD); also elsewhere on the board
/PCM5100 audio/AUDIO_L: C19.2, R7.2; also elsewhere on the board
/PCM5100 audio/AUDIO_R: C20.2, R8.2; also elsewhere on the board
/PCM5100 audio/AVDD: C13.2, C15.1, FB3.2, U9.8 (AVDD)
/PCM5100 audio/DAC_OUTL: R7.1, U9.6 (OUTL)
/PCM5100 audio/DAC_OUTR: R8.1, U9.7 (OUTR)
BCK: U9.13 (BCK); also elsewhere on the board
DIN: U9.14 (DIN); also elsewhere on the board
GND: C12.1, C13.1, C14.1, C15.2, C17.2, C18.2, C19.1, C20.1, C36.2, U9.3 (CPGND), U9.9 (AGND), U9.10 (DEMP), U9.11 (FLT), U9.12 (SCK), U9.16 (FMT), U9.19 (DGND); also elsewhere on the board
LRCK: U9.15 (LRCK); also elsewhere on the board
unnamed: C16.2, U9.4 (CAPM)
unnamed: C16.1, U9.2 (CAPP)
unnamed: C18.1, U9.18 (LDOO)
unnamed: C17.1, U9.5 (VNEG)

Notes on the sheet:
AVDD: +3V3 -> FB3 -> C13 (0.1u) + C15 (10u) at U9 pin 8 (keeps Pico/logic switching noise out of the DAC analogue supply)
C36: CPVDD (U9 pin 1) decoupling, 0.1uF disc close to U9 pins 1 (CPVDD) and 3 (CPGND)

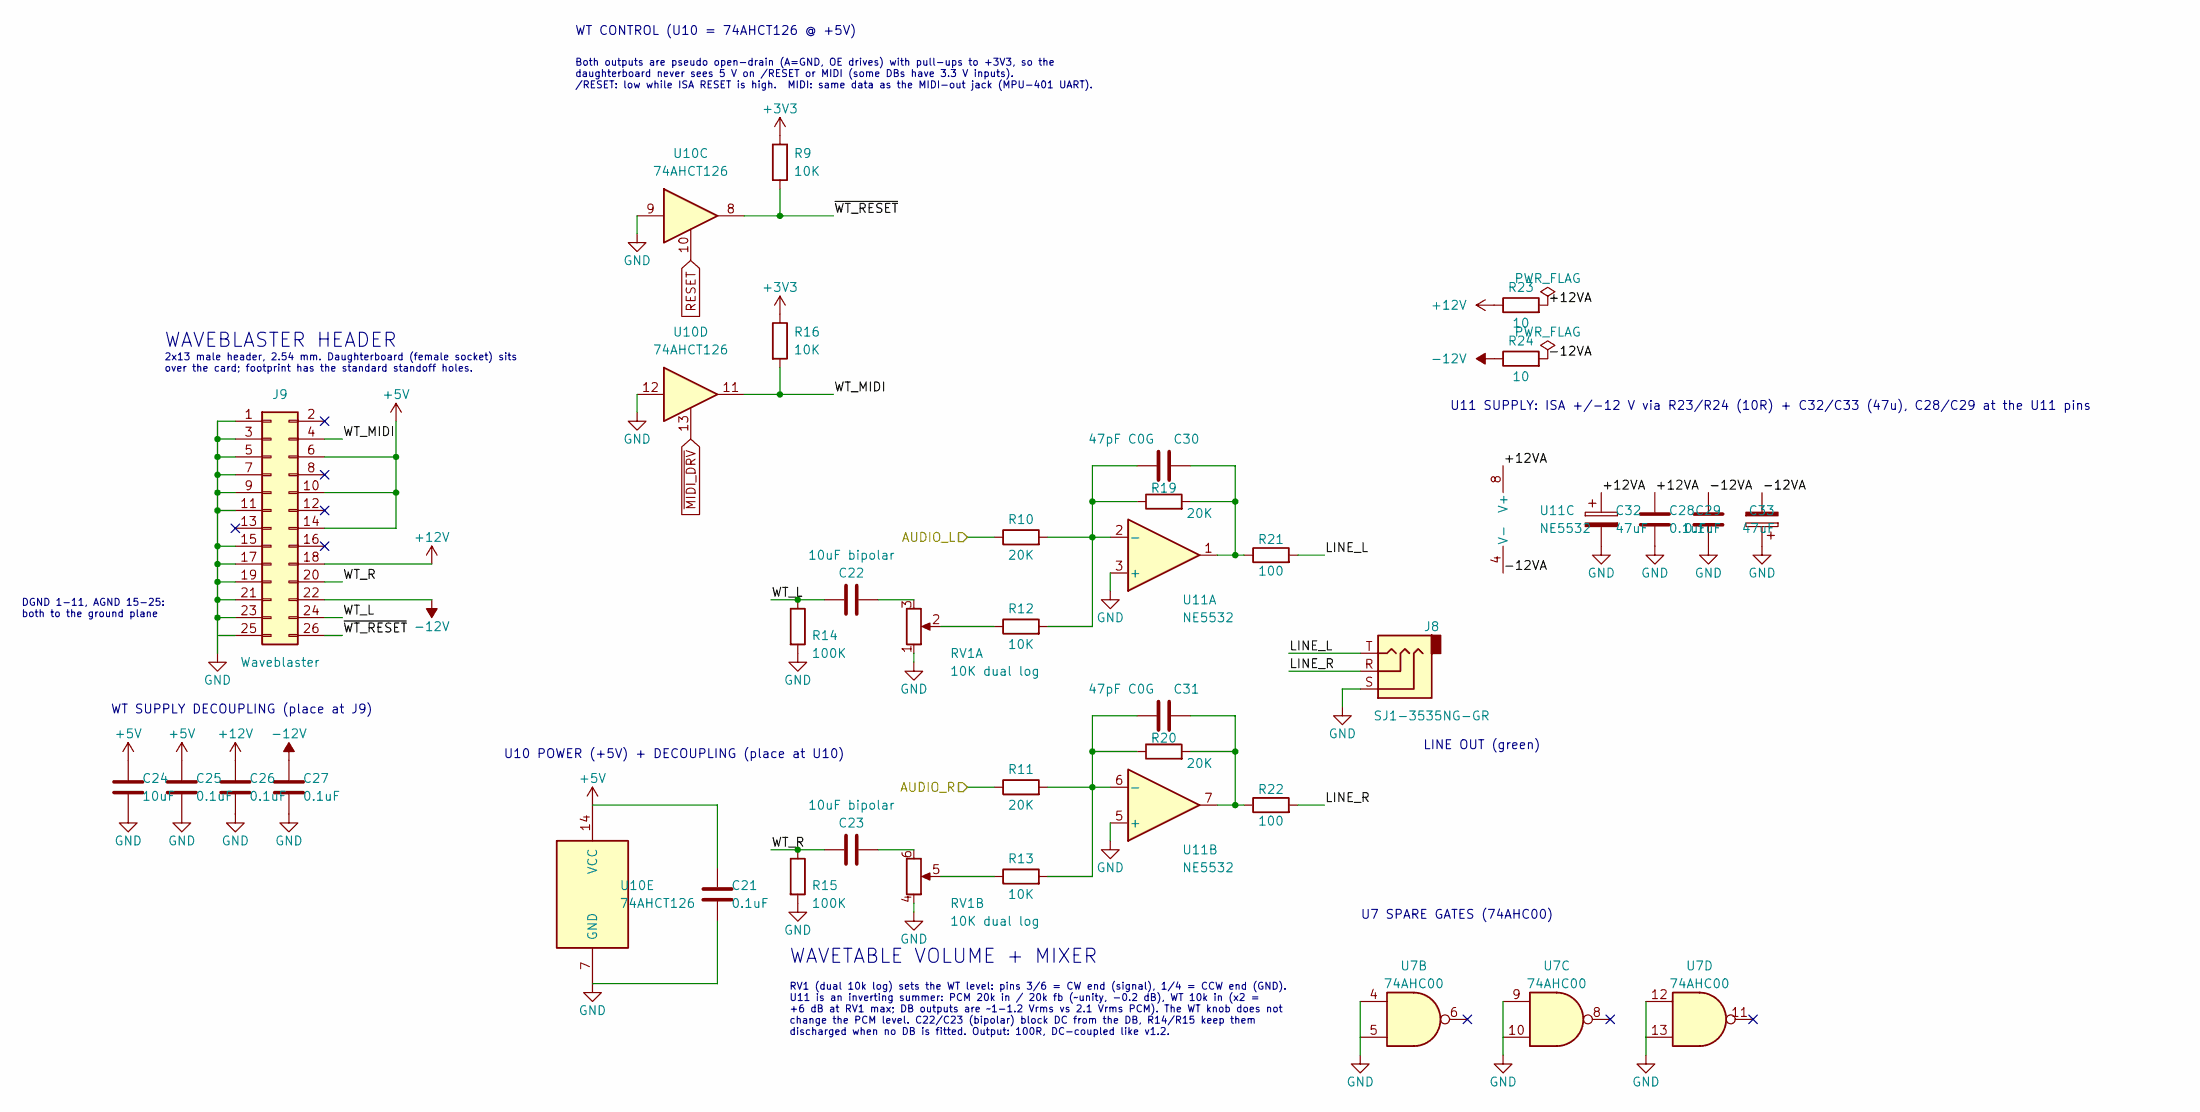
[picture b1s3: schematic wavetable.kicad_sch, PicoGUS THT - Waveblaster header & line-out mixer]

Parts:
C21, C25, C26, C27, C28, C29: 0.1uF; C_Disc_D5.0mm_W2.5mm_P5.00mm; MPN RDER71H104K0M1H03A; DigiKey 490-9144-1-ND
C22, C23: 10uF bipolar; C_Radial_D6.3mm_H11.0mm_P2.50mm; MPN ECE-A1HN100U; DigiKey P1280-ND
C24: 10uF; C_Disc_D5.0mm_W2.5mm_P5.00mm; MPN RCER71H106MWK1H03B; DigiKey 490-11888-ND
C30, C31: 47pF C0G; C_Disc_D5.0mm_W2.5mm_P5.00mm; MPN K470J15C0GF5TH5; DigiKey BC1038CT-ND
C32, C33: 47uF; CP_Radial_D5.0mm_P2.00mm; MPN 35YXJ47M5X11; DigiKey 1189-2919-ND
J8: SJ1-3535NG-GR; Jack_3.5mm_CUI_SJ1-3535NG_Horizontal; MPN SJ1-3535NG-GR; DigiKey CP1-3535NG-GR-ND
J9: Waveblaster; Wavetable_NoMountingHoles; MPN 77313-118-26LF; DigiKey 609-5706-ND
R9, R12, R13, R16: 10K; R_Axial_DIN0207_L6.3mm_D2.5mm_P10.16mm_Horizontal; MPN MFR-25FBF52-10K; DigiKey 10.0KXBK-ND
R10, R11, R19, R20: 20K; R_Axial_DIN0207_L6.3mm_D2.5mm_P10.16mm_Horizontal; MPN MFR-25FBF52-20K; DigiKey 20.0KXBK-ND
R14, R15: 100K; R_Axial_DIN0207_L6.3mm_D2.5mm_P10.16mm_Horizontal; MPN MFR-25FBF52-100K; DigiKey 100KXBK-ND
R21, R22: 100; R_Axial_DIN0207_L6.3mm_D2.5mm_P10.16mm_Horizontal; MPN MFR-25FBF52-100R; DigiKey 100XBK-ND
R23, R24: 10; R_Axial_DIN0207_L6.3mm_D2.5mm_P10.16mm_Horizontal; MPN MFR-25FBF52-10R; DigiKey 10.0XBK-ND
RV1: 10K dual log; Potentiometer_Alps_RK097_Dual_Horizontal_Switch; MPN PTD902-2020K-A103; DigiKey PTD902-2020K-A103-ND
U7: 74AHC00; DIP-14_W7.62mm; MPN SN74AHC00N; DigiKey 296-4510-5-ND
U10: 74AHCT126; DIP-14_W7.62mm; MPN SN74AHCT126N; DigiKey 296-4659-5-ND
U11: NE5532; DIP-8_W7.62mm; MPN NE5532P; DigiKey 296-1410-5-ND

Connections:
+3V3: R9.1, R16.1; also elsewhere on the board
+5V: C21.1, C24.1, C25.1, J9.6, J9.10, J9.14, U10.14 (VCC); also elsewhere on the board
+12V: C26.1, J9.18, R23.1; also elsewhere on the board
-12V: C27.1, J9.22, R24.1; also elsewhere on the board
/PCM5100 audio/AUDIO_L: R10.1; also elsewhere on the board
/PCM5100 audio/AUDIO_R: R11.1; also elsewhere on the board
/Wavetable & line out/+12VA: C28.1, C32.1, R23.2, U11.8 (V+)
/Wavetable & line out/-12VA: C29.2, C33.2, R24.2, U11.4 (V-)
/Wavetable & line out/LINE_L: J8.T, R21.2
/Wavetable & line out/LINE_R: J8.R, R22.2
/Wavetable & line out/WT_L: C22.1, J9.24, R14.1
/Wavetable & line out/WT_MIDI: J9.4, R16.2, U10.11
/Wavetable & line out/WT_R: C23.1, J9.20, R15.1
/Wavetable & line out/~WT_RESET: J9.26, R9.2, U10.8
GND: C21.2, C24.2, C25.2, C26.2, C27.2, C28.2, C29.1, C32.2, C33.1, J8.S, J9.1, J9.3, J9.5, J9.7, J9.9, J9.11, J9.15, J9.17, J9.19, J9.21, J9.23, J9.25, R14.2, R15.2, RV1.1, RV1.4, U7.4, U7.5, U7.9, U7.10, U7.12, U7.13, U10.7 (GND), U10.9, U10.12, U11.3 (+), U11.5 (+); also elsewhere on the board
unnamed: C22.2, RV1.3
unnamed: C23.2, RV1.6
unnamed: C30.2, R19.2, R21.1, U11.1
unnamed: C31.2, R20.2, R22.1, U11.7
unnamed: R12.1, RV1.2
unnamed: R13.1, RV1.5
unnamed: C30.1, R10.2, R12.2, R19.1, U11.2 (-)
unnamed: C31.1, R11.2, R13.2, R20.1, U11.6 (-)
RESET: U10.10; also elsewhere on the board
~MIDI_DRV: U10.13; also elsewhere on the board

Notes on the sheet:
DGND 1-11, AGND 15-25: both to the ground plane
WAVEBLASTER HEADER
2x13 male header, 2.54 mm. Daughterboard (female socket) sits over the card; footprint has the standard standoff holes.
WT SUPPLY DECOUPLING (place at J9)
U10 POWER (+5V) + DECOUPLING (place at U10)
WT CONTROL (U10 = 74AHCT126 @ +5V)
Both outputs are pseudo open-drain (A=GND, OE drives) with pull-ups to +3V3, so the daughterboard never sees 5 V on /RESET or MIDI (some DBs have 3.3 V inputs). /RESET: low while ISA RESET is high. MIDI: same data as the MIDI-out jack (MPU-401 UART).
U11 SUPPLY: ISA +/-12 V via R23/R24 (10R) + C32/C33 (47u), C28/C29 at the U11 pins
WAVETABLE VOLUME + MIXER
RV1 (dual 10k log) sets the WT level: pins 3/6 = CW end (signal), 1/4 = CCW end (GND). U11 is an inverting summer: PCM 20k in / 20k fb (~unity, -0.2 dB), WT 10k in (x2 = +6 dB at RV1 max; DB outputs are ~1-1.2 Vrms vs 2.1 Vrms PCM). The WT knob does not change the PCM level. C22/C23 (bipolar) block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
LINE OUT (green)
U7 SPARE GATES (74AHC00)

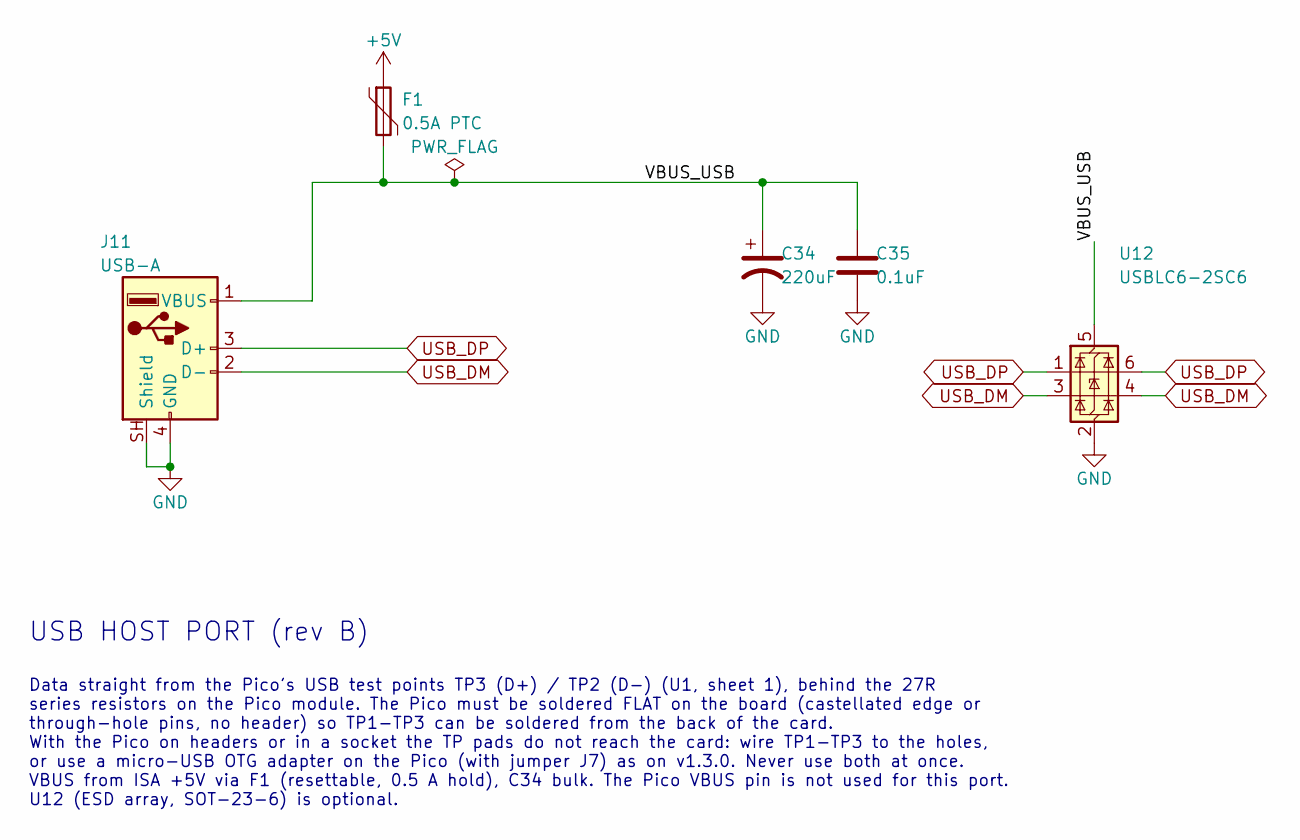
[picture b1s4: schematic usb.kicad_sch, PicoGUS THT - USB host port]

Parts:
C34: 220uF; CP_Radial_D6.3mm_P2.50mm; MPN 16ZLH220MEFC6.3X11; DigiKey 1189-1726-ND
C35: 0.1uF; C_Disc_D5.0mm_W2.5mm_P5.00mm; MPN RDER71H104K0M1H03A; DigiKey 490-9144-1-ND
F1: 0.5A PTC; Fuse_Bourns_MF-RHT050; MPN MF-R050; DigiKey MF-R050-ND
J11: USB-A; USB_A_Molex_67643_Horizontal; MPN 0676430910; DigiKey WM4993-ND
U12: USBLC6-2SC6; SOT-23-6; MPN USBLC6-2SC6; DigiKey 497-5235-1-ND

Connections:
+5V: F1.1; also elsewhere on the board
/USB host port/VBUS_USB: C34.1, C35.1, F1.2, J11.1 (VBUS), U12.5 (VBUS)
GND: C34.2, C35.2, J11.4 (GND), J11.SH (Shield), U12.2 (GND); also elsewhere on the board
USB_DM: J11.2 (D-), U12.3 (I/O2), U12.4 (I/O2); also elsewhere on the board
USB_DP: J11.3 (D+), U12.1 (I/O1), U12.6 (I/O1); also elsewhere on the board

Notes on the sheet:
USB HOST PORT (rev B)
Data straight from the Pico's USB test points TP3 (D+) / TP2 (D-) (U1, sheet 1), behind the 27R series resistors on the Pico module. The Pico must be soldered FLAT on the board (castellated edge or through-hole pins, no header) so TP1-TP3 can be soldered from the back of the card. With the Pico on 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

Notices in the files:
hw-ne2k/PicoGUS-NE2K.kicad_pcb:
© 2023-2026 Ian Scott (polpo),
Vidar Waagbø (waagbo)
Licensed under CERN-OHL-P v2
hw-tht-v1.3/PicoGUS-THT.kicad_pcb:
© 2023-2026 Ian Scott (polpo), Vidar Waagbø (waagbo)
